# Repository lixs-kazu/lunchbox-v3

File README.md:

# lunchbox-v3

ボトムプレートは３Dプリントお願いします．

インサートは　黄銅 ビットインサート・スタンダード型・方向指定なし M2D1 3.0D2 3.3L30 (https://wilco.jp/products/B/HSB-Z.html#page4)
を二液混合型のエポキシパテで固めています．

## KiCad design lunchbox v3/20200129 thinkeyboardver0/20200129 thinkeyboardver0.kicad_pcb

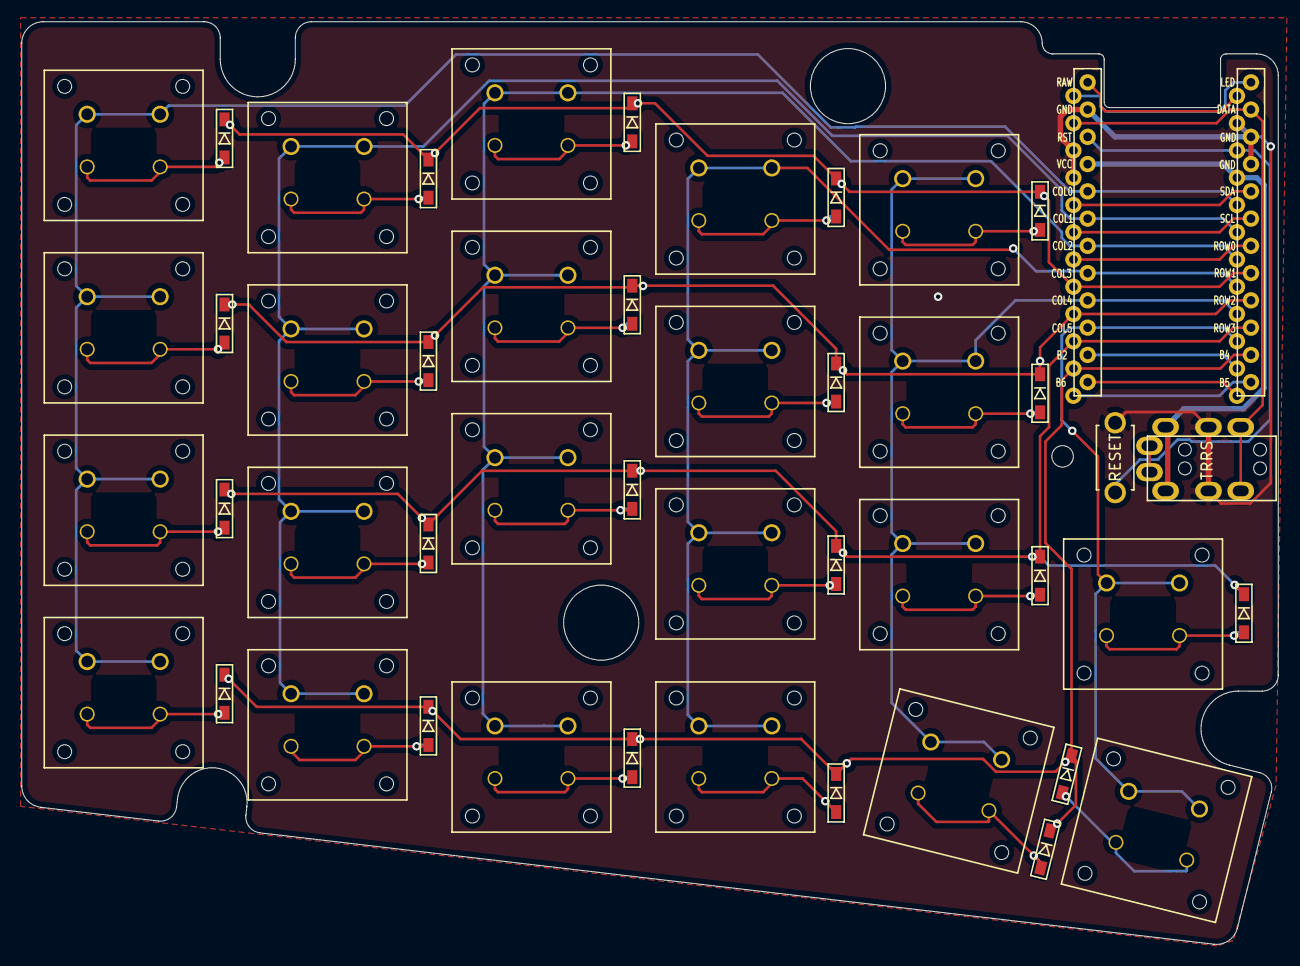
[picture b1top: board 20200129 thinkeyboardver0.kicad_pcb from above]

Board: 2 copper layers, 117.1 x 86.0 mm, 47 parts (0 on the bottom side), 36 nets.

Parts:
D1, D2, D3, D4, D5, D6, D7, D8, D9, D10, D11, D12, D13, D14, D15, D16, D17, D18, D19, D20, D21, D22: D; D3_SMD
J1: MJ-4PP-9
SW1, SW2, SW3, SW4, SW5, SW6, SW7, SW8, SW9, SW10, SW11, SW12, SW13, SW14, SW15, SW16, SW17, SW18, SW19, SW20, SW21, SW22: SW_PUSH; Kailh-PG1425-X-Switch-reversible
SW23: SW_PUSH; ResetSW
U1: ProMicro; ProMicro_v2

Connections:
GND: J1.C, SW23.1, U1.3, U1.4, U1.23
unnamed: D1.2, SW1.2
unnamed: D2.2, SW2.2
unnamed: D3.2, SW3.2
unnamed: D4.2, SW4.2
unnamed: D5.2, SW5.2
unnamed: D6.2, SW6.2
unnamed: D7.2, SW7.2
unnamed: D8.2, SW8.2
unnamed: D9.2, SW9.2
unnamed: D10.2, SW10.2
unnamed: D11.2, SW11.2
unnamed: D12.2, SW12.2
unnamed: D13.2, SW13.2
unnamed: D14.2, SW14.2
unnamed: D15.2, SW15.2
unnamed: D16.2, SW16.2
unnamed: D17.2, SW17.2
unnamed: D18.2, SW18.2
unnamed: D19.2, SW19.2
unnamed: D20.2, SW20.2
unnamed: D21.2, SW21.2
unnamed: D22.2, SW22.2
RST: SW23.2, U1.22
VCC: J1.D, U1.21
col0: SW1.1, SW2.1, SW3.1, SW4.1, U1.20
col1: SW5.1, SW6.1, SW7.1, SW8.1, U1.19
col2: SW9.1, SW10.1, SW11.1, SW12.1, U1.18
col3: SW13.1, SW14.1, SW15.1, SW16.1, U1.17
col4: SW17.1, SW18.1, SW19.1, SW20.1, U1.16
col5: SW21.1, SW22.1, U1.15
date: J1.B, U1.2
row1: D1.1, D5.1, D9.1, D13.1, D17.1, U1.8
row2: D2.1, D6.1, D10.1, D14.1, D18.1, U1.9
row3: D3.1, D7.1, D11.1, D15.1, D19.1, D21.1, U1.10
row4: D4.1, D8.1, D12.1, D16.1, D20.1, D22.1, U1.11

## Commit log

2021-06-20 Create PCB
